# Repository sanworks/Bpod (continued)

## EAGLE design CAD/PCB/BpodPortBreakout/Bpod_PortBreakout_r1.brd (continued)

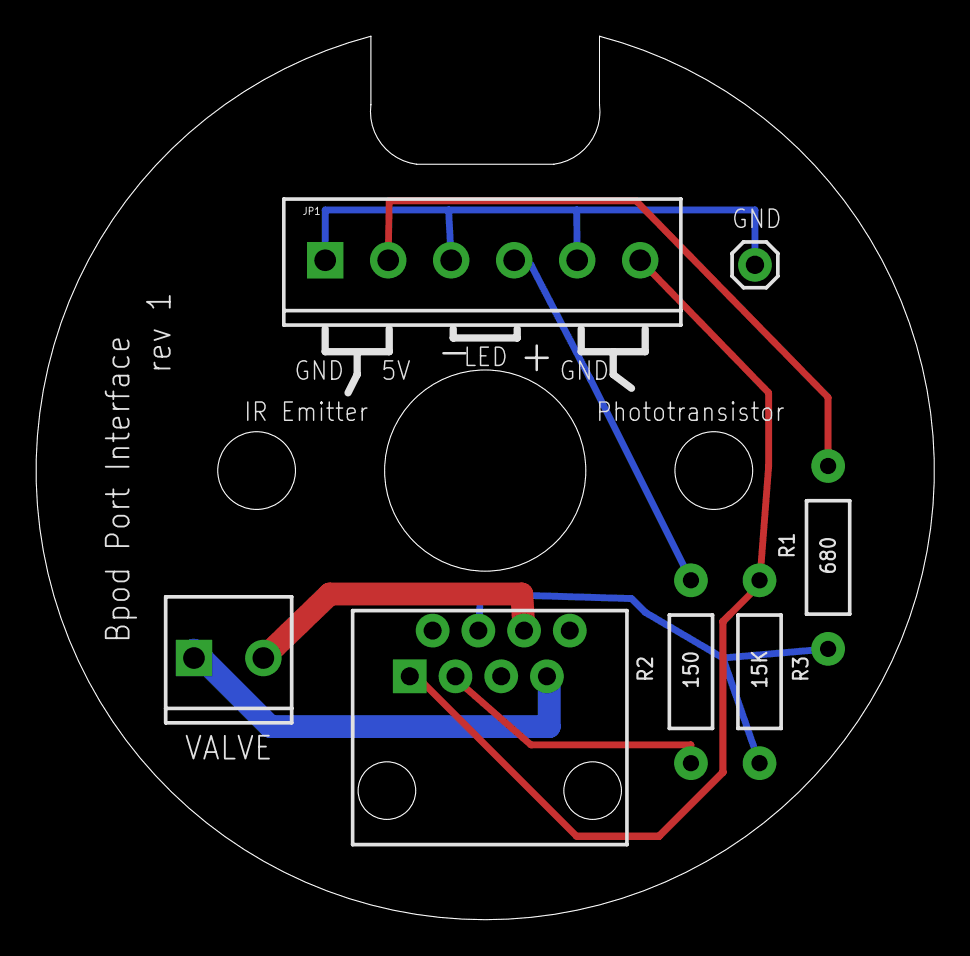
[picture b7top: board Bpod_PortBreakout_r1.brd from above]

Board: 2 copper layers, 49.9 x 49.1 mm, 7 parts (0 on the bottom side), 8 nets.

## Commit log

2016-04-23 Firmware: -Switched digital reads to digitalReadDirect (less overhead than Arduino builtin) -Added functions to write 16 and 32 bit ints over serial (replacing clunkier code) -Fixed soft-code handlin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
2016-04-25 -Added more comments to example protocols -Added a simple example 2AFC protocol based on light -Removed the auditory tuning curve mapping protocol (not general) -Updated license info
2016-04-27 -In firmware, fixed handling of simultaneous events captured during a single 100us cycle. (Previously, only the first event could possibly trigger a state transition.) -Fixed an incorrectly named var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
2016-04-27 -Fixed virtual poke and logic event functionality. (disabled in previous version) -Updated comments describing state matrix columns (in firmware) -Resized input matrix to match data (in firmware) -Fi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
    Thanks to Tim Hanks at UC Davis for beta-testing like a pro!! The fixes in this push and the previous push were in response to his validation work.
2016-05-01 Fixed a bug in Bpod Emulator (false global counter events), created in previous push.
2016-05-11 -Restored hardware serial override functionality from console GUI -Replaced waitforbytes...readbytes sequences with functions to read different int datatypes in main module firmware
2016-05-11 -Fixed last event display
2016-05-12 -Set default input config to 3 ports connected -Fixed conflicted global variable usage in firmware. Fixes a bug from last push - fixes hardware serial override.
2016-05-16 -Updated mouse port design to remove copolyester material in the infrared beam path.
2016-05-25 -Fixes default volume in TeensySoundServer plugin -Fixes to make Bpod compatible with Windows 10 -Fixed Bonsai plugin - added buffer flush on state matrix start
2016-06-10 -Added serial port auto-discovery for mac (contributed by Thiago Gouvea, Kepecs Lab, CSHL) -Deleted behavior data files
2016-07-06 Added STL files for mouse port, sheath and mount
2016-07-07 -Added firmware for Bpod main module 0.6 (changed components to equivalent SMT - firmware changes only affect optocoupler readout) -Added design for a mouse port with a second tube for air delivery
2016-07-14 -Updated r0.6 firmware to use ArCOM, to add comments and to optimize USB data transfer times -Fixed example matrices -Updated default input config for 3 ports -Added simple "light chasing" example pr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
2016-07-18 Fixed BNC output bit logic in 0.6 firmware (bug from previous push)
2016-07-28 -Updated design for mouse box port breakout board -Added a surface mount version of the port breakout board
2016-08-04 Added SaveProtocolSettings, a function accessed from the launch manager to save parameter structs after editing.
2016-08-19 -Revised nosepoke design to fit M4 screws and 15ga steel tube for liquid delivery
2016-08-22 Increased mouse port depth (beyond photogate) by 0.8mm to match original version
2016-08-23 -Adjusted depth of mouse port LED for more uniform illumintation -Adjusted diameter of mouse port sheath for better press fit -Added mouse port sheath slicer settings (Cura)
2016-10-11 Bpod 0.7 beta - initial commit
2016-10-16 -Reorganized example protocols
2016-10-19 -Fixed global timers, counters and conditions in Bpod emulator -Renamed serial example from BpodUartControl to BpodUart2SerialUSBTerm
2016-10-19 -Fixed bug where Bpod font installation was not detected on some systems
2016-10-22 -Added PCB design files for Bpod 0.7
2016-11-09 -Added I2C Messenger module for Bpod 0.7
2016-11-23 -Added hardware abstraction to state machine firmware and MATLAB code -Restored support for Bpod 0.5 -Moved CAD to separate repository -Moved Protocols, Settings and Calibration data to configurable 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
2016-11-29 -Fixed bug in pause function
2016-11-29 -Removed redundant timestamp transfer from firmware and RunStateMachine (requires firmware update) -Added firmware update alert, if incompatible firmware is detected. This alert will not work for Bpo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
2016-12-04 -Fixed bug with serial port auto-detect when multiple serial devices are present -Fixed LoadSerialMessages function for case when one message is being loaded (instead of a cell array of strings) -Cor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
2016-12-05 -Added alpha version of Python client for Bpod (command line only) -Removed comments in AddTrialEvents (MATLAB)
2016-12-21 -Fixed font installation code on Ubuntu 16.
2017-01-13 -Added features to global timers: onsetDelay, [timer]_Start event, timer start and end can control output channels (digital, serial) -Optimized trial type outcome plot for speed -Optimized state mach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
2017-01-18 Restored option to force Bpod to use MATLAB's Java serial interface (default = PsychToolbox if present) by calling Bpod('COM3', 'ForceJava'). This option is intended for debugging psychtoolbox instal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
2017-02-01 -Added support for Bpod analog output module -Added module integration scheme: on Bpod start, state machine polls modules for information by sending byte 255. Modules return names and firmware versio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
2017-02-02 -Updated module info scheme for robustness and simplified code to detect future extensions. Module first returns character 'A' (Acknowledge), followed by firmware version, followed by name length, fo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
2017-02-02 -Fixed microSD card initialization (previously wrote only 1 byte for each sample; samples are 2 bytes)
2017-02-05 -Added PulsePalModule firmware and MATLAB API, to add Pulse Pal functionality to the Bpod analog output module
2017-02-06 -Renamed trigger mode: 'Godmode' to 'Master' mode
2017-02-09 -Fixed trigger 'Toggle' mode in WavePlayer firmware - previously voltage did not always return to 0 when toggled off -Fixed trigger 'Master' mode in WavePlayer firmware - previously one buffer worth 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
2017-03-07 -Increased number of serial events from 10 to 15 for Pocket State Machine -Updated choice wheel module firmware -Added closed-loop analog example firmware using Arduino M0 as an analog input module -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
2017-03-10 -Finalized ValveDriverModule serial interface
2017-03-10 -Added ability to call LoadSerialMessages with module name (instead of physical serial port) as first argument
2017-03-10 -Set state machine firmware to clear serial message library when Bpod application launches
2017-03-31 -Added tabbed override panels to console (each module's panel is loaded from /Bpod/Functions/Override Panels/) -Added default override panel for modules that don't have one - a functional serial term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
2017-04-02 -Updated DDS module firmware -Added DDS module MATLAB plugin
2017-04-03 -Fixed bug that dropped serial bytes from new UI serial terminal if more than 8 were sent at once (requires firmware update) -Improved echo module firmware, to use buffered reads and writes, greatly 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
2017-04-07 -Added bit-to-frequency mapping support for state machine and USB control (previously input module only) -Added support for fractional frequency tuning from USB and state machine
2017-04-07 -Fixed Bpod Emulator bug - now skips code related to module relay setup/enable/disable if running the emulator
2017-04-09 -Updated PsychToolboxVideoServer to match documentation. This is a major change that affects how parameters are interpreted.
2017-04-11 -Removed an orphan function from NewLaunchManager.m
2017-04-16 -Added Trial Manager object. Trial Manager provides an alternative to RunStateMachine() that reduces dead-time by processing plots, saving data, etc. while trials are running. -Added an example proto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
2017-04-25 -NOTE: THIS PUSH REQUIRES FIRMWARE UPDATE for state machine AND all modules. -Modules that send a module name and firmware version back must now include a byte 0x0 after the "module info" message, to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
    Updates:
    -Added ability for modules to request more than the default number of events (up to a maximum for all modules specified in state machine firmware).
    -Added ability for modules to send event names (to replace byte numbers in default module events scheme, e.g. for a lever module, ModuleName1_1 --> ModuleName1_Press.) See SNES module for an example 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
2017-04-27 -Fixed emulator bug on startup, introduced on last commit
2017-04-28 -Bug fixes to Bpod emulator (In previous fix, emulator had incorrect channel mapping for Bpod 0.7/0.8)
2017-05-04 -Added CurrentSubjectName field to BpodSystem.Status struct -Fixed "Camel Case" detection code in module name formatting displayed on launch manager tabs
2017-05-05 -Disabled java UI hack for console tabs that does not work on MATLAB r2016a or newer.
2017-05-08 -Made new launch manager Java UI hacks conditional, to not run on MATLAB r2016a+
2017-05-09 -Fixed bug affecting number of global timers detected by SetGlobalTimer function.
2017-05-11 -Fixed bug in firmware related to global timers. If a zero onset delay (or no onset delay) was chosen in the timer declaration, the timer would start on trial start, not when triggered (if triggered 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
2017-05-19 -Added firmware option to disable status indicator LED on Bpod state machine
2017-05-22 -Added analog closed loop firmware example for analog input and output modules. Contains tailored Arduino libraries for both the AD7327 ADC and the AD5754R DAC. -Added PulsePal firmware for analog ou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
2017-05-25 -Added firmware and Bpod plugin for analog input module -When a Bpod console module panel's serial terminal is in "byte" mode, bytes are displayed as space delimited numbers (previously ASCII, as in 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
2017-05-25 -Fixed a temporary hack that forced the analog input module to use Java serial
2017-05-25 -Fixed text on analog input module scope UI
2017-05-26 -Disabled some parameter changes during microSD data logging with analog input module: sampling rate, range, #sampled channels and #samples to acquire. -Added improved comments to analog input module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
2017-05-29 -Renamed some fields of analog input object for clarity, now synchronized with documentation
2017-06-11 -Updated DDS module firmware to fix a bug with amplitude selection -Added DDSSequencer firmware, to play patterns of up to 10,000 discrete sine or triangle wave pulses on trigger.
